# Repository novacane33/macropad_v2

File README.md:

# macropad_v2
***Changes req for v3:***
Optimise PCB space,
Optimise switch spacing,
Add mounting holes to secure board in case

Simple macropad with 9 keys and 2 rotary encoders.

Changes from v1:
Added rotary encoders

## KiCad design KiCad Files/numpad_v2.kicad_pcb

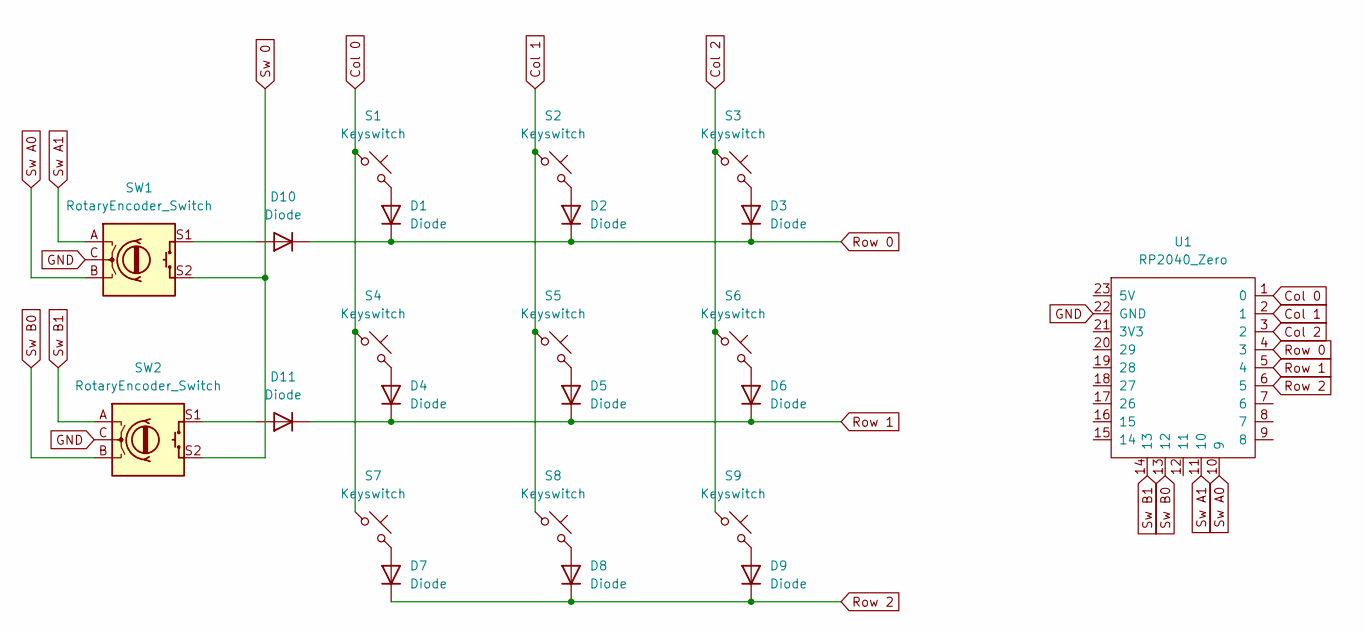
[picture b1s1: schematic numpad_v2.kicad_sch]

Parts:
D1, D2, D3, D4, D5, D6, D7, D8, D9, D10, D11: Diode; Diode_DO-35
S1, S2, S3, S4, S5, S6, S7, S8, S9: Keyswitch; MX_PCB
SW1, SW2: RotaryEncoder_Switch; Encoder_EC11_MX
U1: RP2040_Zero

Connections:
Col 0: S1.1, S4.1, S7.1, U1.1 (0)
Col 1: S2.1, S5.1, S8.1, U1.2 (1)
Col 2: S3.1, S6.1, S9.1, U1.3 (2)
GND: SW1.C, SW2.C, U1.22 (GND)
unnamed: D1.2 (A), S1.2
unnamed: D2.2 (A), S2.2
unnamed: D3.2 (A), S3.2
unnamed: D4.2 (A), S4.2
unnamed: D5.2 (A), S5.2
unnamed: D6.2 (A), S6.2
unnamed: D7.2 (A), S7.2
unnamed: D8.2 (A), S8.2
unnamed: D9.2 (A), S9.2
unnamed: D10.2 (A), SW1.S1
unnamed: D11.2 (A), SW2.S1
Row 0: D1.1 (K), D2.1 (K), D3.1 (K), D10.1 (K), U1.4 (3)
Row 1: D4.1 (K), D5.1 (K), D6.1 (K), D11.1 (K), U1.5 (4)
Row 2: D7.1 (K), D8.1 (K), D9.1 (K), U1.6 (5)
Sw 0: SW1.S2, SW2.S2
Sw A0: SW1.B, U1.10 (9)
Sw A1: SW1.A, U1.11 (10)
Sw B0: SW2.B, U1.13 (12)
Sw B1: SW2.A, U1.14 (13)

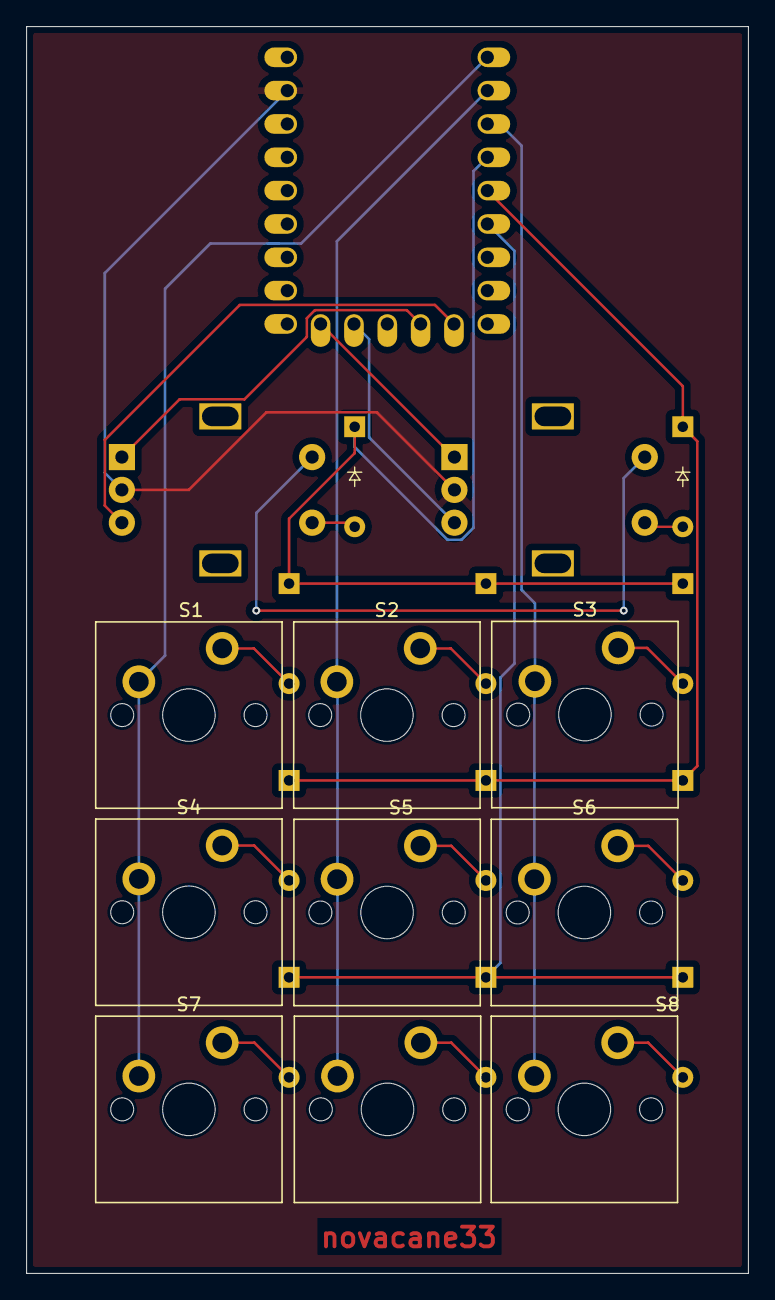
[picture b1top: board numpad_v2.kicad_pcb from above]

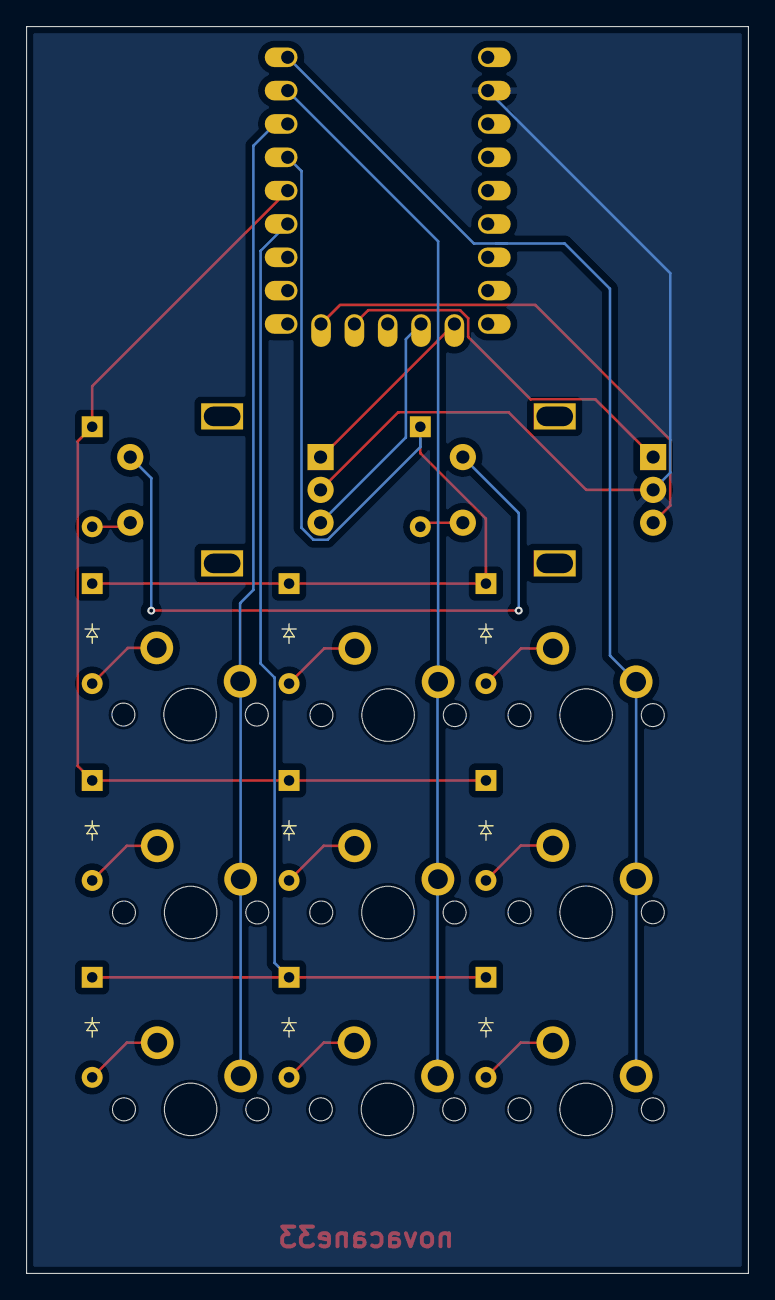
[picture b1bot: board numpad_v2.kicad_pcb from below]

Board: 2 copper layers, 55.0 x 95.0 mm, 23 parts (9 on the bottom side), 23 nets.

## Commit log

2025-03-27 CAD files
